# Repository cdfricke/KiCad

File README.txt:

Connor Fricke (cd.fricke23@gmail.com)
4-June-2024

KiCad projects designed and developed as part of assistant
research work within the Beatty Lab Group at Ohio State University.

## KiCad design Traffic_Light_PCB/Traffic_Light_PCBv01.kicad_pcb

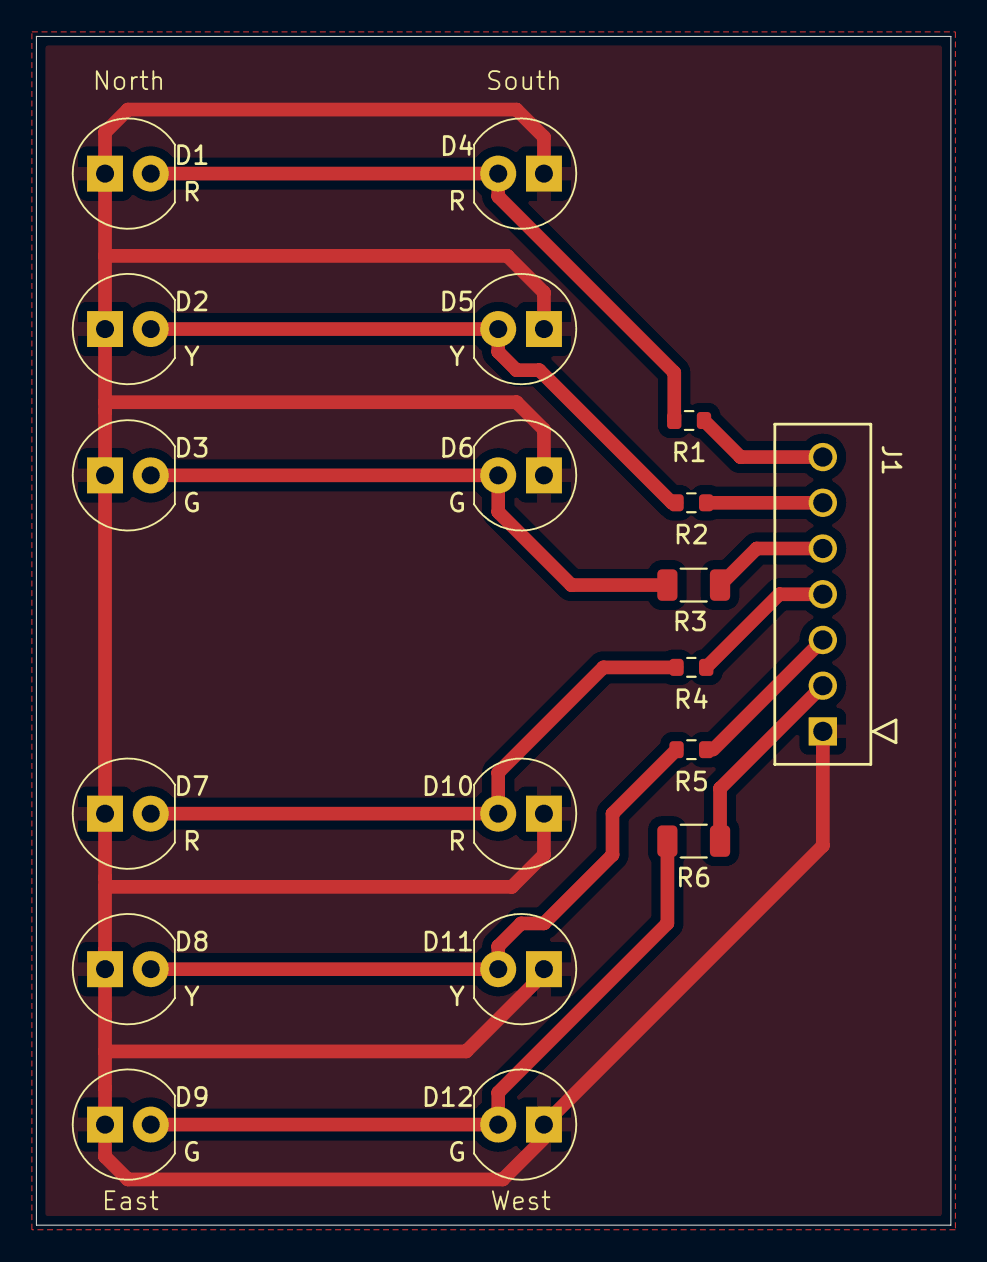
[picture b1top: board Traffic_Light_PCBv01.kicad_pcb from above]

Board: 2 copper layers, 50.8 x 66.0 mm, 19 parts (0 on the bottom side), 13 nets.

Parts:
D1, D4, D7, D10: R; LED_5mm_Radial
D2, D5, D8, D11: Y; LED_5mm_Radial
D3, D6, D9, D12: G; LED_5mm_Radial
J1: 7PIN-HEADER
R1, R2, R4, R5: 100; R_0603_1608Metric
R3, R6: 10; R_1206_3216Metric

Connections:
/EW_GREEN: J1.2, R6.1
/EW_RED: J1.4, R4.1
/EW_YELLOW: J1.3, R5.1
/NS_GREEN: J1.5, R3.1
/NS_RED: J1.7, R1.1
/NS_YELLOW: J1.6, R2.1
GND: D1.1 (K), D2.1 (K), D3.1 (K), D4.1 (K), D5.1 (K), D6.1 (K), D7.1 (K), D8.1 (K), D9.1 (K), D10.1 (K), D11.1 (K), D12.1 (K), J1.1
unnamed: D1.2 (A), D4.2 (A), R1.2
unnamed: D2.2 (A), D5.2 (A), R2.2
unnamed: D3.2 (A), D6.2 (A), R3.2
unnamed: D7.2 (A), D10.2 (A), R4.2
unnamed: D8.2 (A), D11.2 (A), R5.2
unnamed: D9.2 (A), D12.2 (A), R6.2
